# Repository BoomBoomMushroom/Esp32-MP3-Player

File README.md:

# ESP32 MP3 Player
An MP3 Player powered by an ESP32, with both bluetooth and a speaker output

I made this project because I want to move away from Spotify and own the songs I play. I have bought a dozen or two songs from bandcamp and that will be whats played on this!

Video of it working (Nothing here yet, still need funding)

Features:
- Seeed studio ESP32-S3 plus for the MCU and battery charging circuit
- A 2.8in ili9341 tft color screen
- MAX17048G+T10 for battery level checking
- a rotary encoder for input, and a vol up and vol down button
- MAX98357A + 8ohm 3W speakers for use w/o bluetooth headphones/speakers
- Any single cell LiPo works, im probably going to use a 2000mAh or 3000mAh battery

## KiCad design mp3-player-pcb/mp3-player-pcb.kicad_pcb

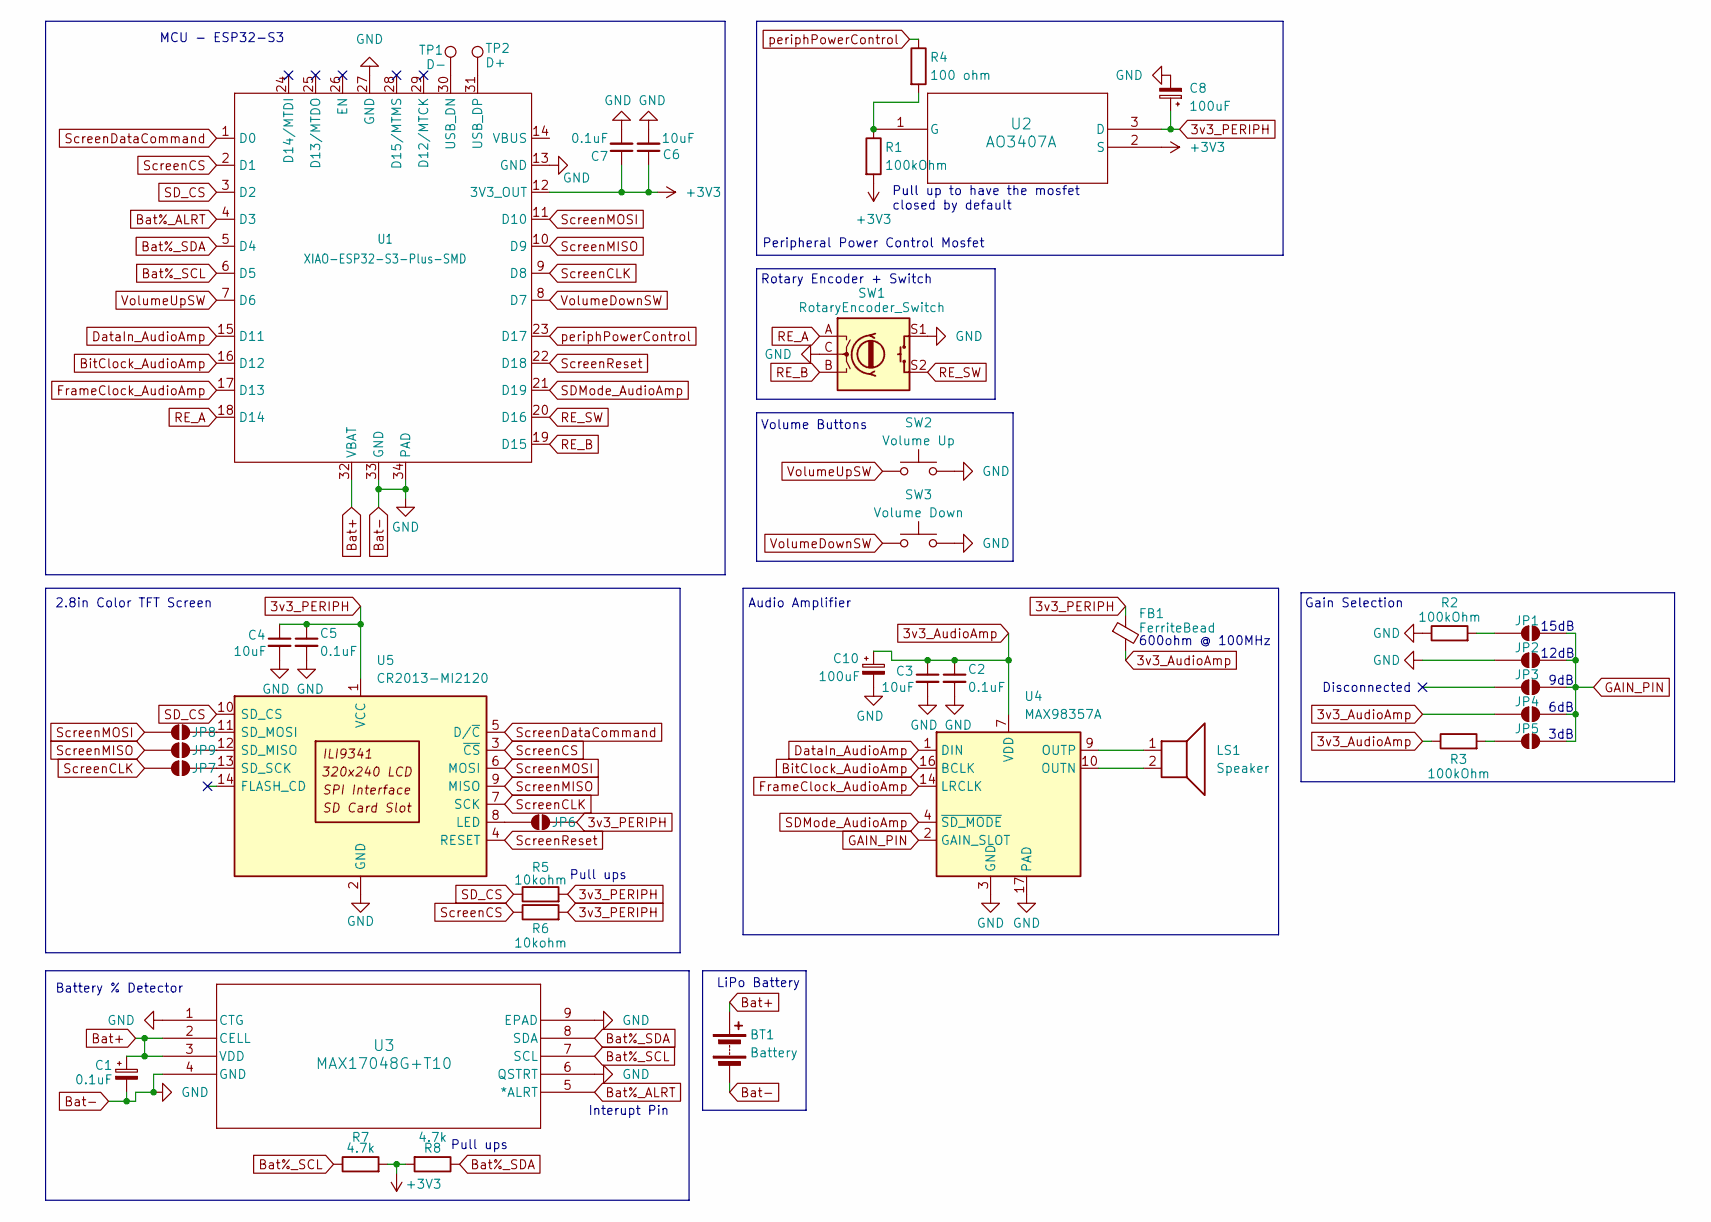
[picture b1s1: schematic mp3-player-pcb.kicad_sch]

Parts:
BT1: Battery; JST_EH_B2B-EH-A_1x02_P2.50mm_Vertical
C1: 0.1uF; CP_Radial_D4.0mm_P2.00mm
C2, C5, C7: 0.1uF; C_0603_1608Metric_Pad1.08x0.95mm_HandSolder
C3, C4, C6: 10uF; C_0603_1608Metric_Pad1.08x0.95mm_HandSolder
C8, C10: 100uF; CP_Radial_D4.0mm_P2.00mm
FB1: FerriteBead; C_0805_2012Metric_Pad1.18x1.45mm_HandSolder
JP1, JP2, JP3, JP4, JP5, JP6, JP7, JP8, JP9: SolderJumper_2_Open; SolderJumper-2_P1.3mm_Open_Pad1.0x1.5mm
LS1: Speaker; PinHeader_1x02_P2.54mm_Vertical
R1, R2, R3: 100kOhm; R_Axial_DIN0204_L3.6mm_D1.6mm_P5.08mm_Horizontal
R4: 100 ohm; R_Axial_DIN0204_L3.6mm_D1.6mm_P5.08mm_Horizontal
R5, R6: 10kohm; R_Axial_DIN0204_L3.6mm_D1.6mm_P5.08mm_Horizontal
R7, R8: 4.7k; R_Axial_DIN0204_L3.6mm_D1.6mm_P5.08mm_Horizontal
SW1: RotaryEncoder_Switch; RotaryEncoder_Bourns_Vertical_PEC12R-3x17F-Sxxxx
SW2: Volume Up; SW_Tactile_SPST_Angled_PTS645Vx58-2LFS
SW3: Volume Down; SW_Tactile_SPST_Angled_PTS645Vx58-2LFS
TP1: D-; TestPoint_Pad_D1.5mm
TP2: D+; TestPoint_Pad_D1.5mm
U1: XIAO-ESP32-S3-Plus-SMD
U2: AO3407A; SOT-23-3L_AOS
U3: MAX17048G+T10; 21-0168E_T822-3_MXM
U4: MAX98357A; TQFN-16-1EP_3x3mm_P0.5mm_EP1.23x1.23mm
U5: CR2013-MI2120

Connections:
3v3_AudioAmp: C2.1, C3.1, C10.1, FB1.2, JP4.1 (A), R3.1, U4.7 (VDD), U4.8 (VDD)
3v3_PERIPH: C4.1, C5.1, C8.1, FB1.1, JP6.2 (B), R5.2, R6.2, U2.3 (D), U5.1 (VCC)
+3V3: C6.1, C7.1, R1.2, R7.2, R8.2, U1.12 (3V3_OUT), U2.2 (S)
Bat%_ALRT: U1.4 (D3), U3.5 (*ALRT)
Bat%_SCL: R7.1, U1.6 (D5), U3.7 (SCL)
Bat%_SDA: R8.1, U1.5 (D4), U3.8 (SDA)
Bat+: BT1.1 (+), C1.1, U1.32 (VBAT), U3.2 (CELL), U3.3 (VDD)
Bat-: BT1.2 (-), C1.2, C2.2, C3.2, C4.2, C5.2, C6.2, C7.2, C8.2, C10.2, JP2.1 (A), R2.1, SW1.C, SW1.S1, SW2.2, SW3.2, U1.13 (GND), U1.27 (GND), U1.33 (GND), U1.34 (PAD), U3.1 (CTG), U3.4 (GND), U3.6 (QSTRT), U3.9 (EPAD), U4.3 (GND), U4.11 (GND), U4.15 (GND), U4.17 (PAD), U5.2 (GND)
BitClock_AudioAmp: U1.16 (D12), U4.16 (BCLK)
DataIn_AudioAmp: U1.15 (D11), U4.1 (DIN)
FrameClock_AudioAmp: U1.17 (D13), U4.14 (LRCLK)
GAIN_PIN: JP1.2 (B), JP2.2 (B), JP3.2 (B_2), JP4.2 (B), JP5.2 (B), U4.2 (GAIN_SLOT)
unnamed: JP1.1 (A), R2.2
unnamed: JP5.1 (A), R3.2
unnamed: JP6.1 (A), U5.8 (LED)
unnamed: JP7.2 (B), U5.13 (SD_SCK)
unnamed: JP8.2 (B), U5.11 (SD_MOSI)
unnamed: JP9.2 (B), U5.12 (SD_MISO)
unnamed: TP1.1 (1_1), U1.30 (USB_DN)
unnamed: TP2.1 (1_1), U1.31 (USB_DP)
unnamed: R1.1, R4.2, U2.1 (G)
unnamed: LS1.2, U4.10 (OUTN)
unnamed: LS1.1, U4.9 (OUTP)
RE_A: SW1.A, U1.18 (D14)
RE_B: SW1.B, U1.19 (D15)
RE_SW: SW1.S2, U1.20 (D16)
SDMode_AudioAmp: U1.21 (D19), U4.4 (~SD_MODE)
SD_CS: R5.1, U1.3 (D2), U5.10 (SD_CS)
ScreenCLK: JP7.1 (A), U1.9 (D8), U5.7 (SCK)
ScreenCS: R6.1, U1.2 (D1), U5.3 (~CS)
ScreenDataCommand: U1.1 (D0), U5.5 (D/~C)
ScreenMISO: JP9.1 (A), U1.10 (D9), U5.9 (MISO)
ScreenMOSI: JP8.1 (A), U1.11 (D10), U5.6 (MOSI)
ScreenReset: U1.22 (D18), U5.4 (RESET)
VolumeDownSW: SW3.1, U1.8 (D7)
VolumeUpSW: SW2.1, U1.7 (D6)
periphPowerControl: R4.1, U1.23 (D17)

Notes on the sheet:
Pull up to have the mosfet closed by default
600ohm @ 100MHz
2.8in Color TFT Screen
Volume Buttons
Rotary Encoder + Switch
6dB
Battery % Detector
Audio Amplifier
9dB
12dB
MCU - ESP32-S3
3dB
Gain Selection
Disconnected
Interupt Pin
Pull ups
LiPo Battery
15dB
Peripheral Power Control Mosfet

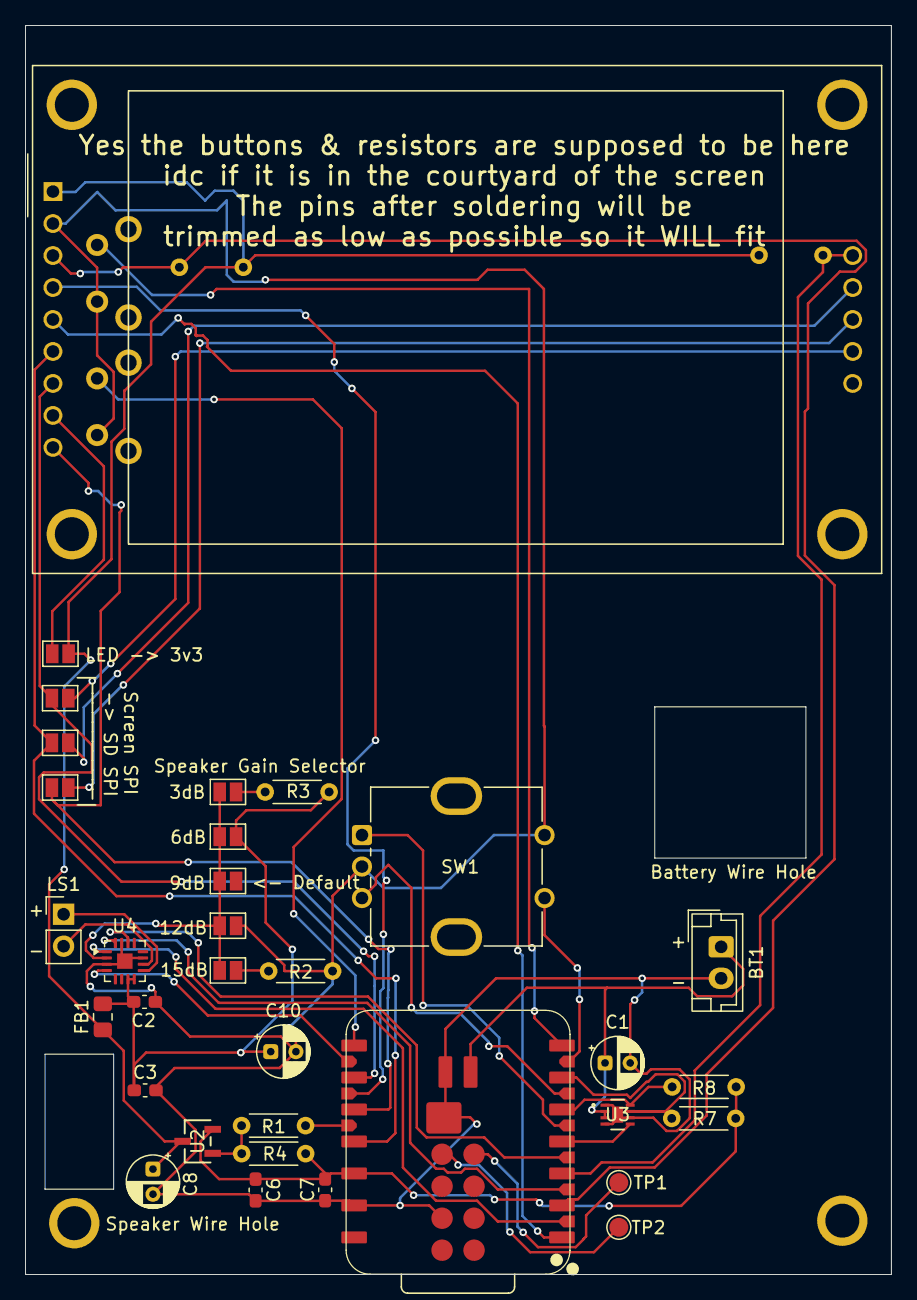
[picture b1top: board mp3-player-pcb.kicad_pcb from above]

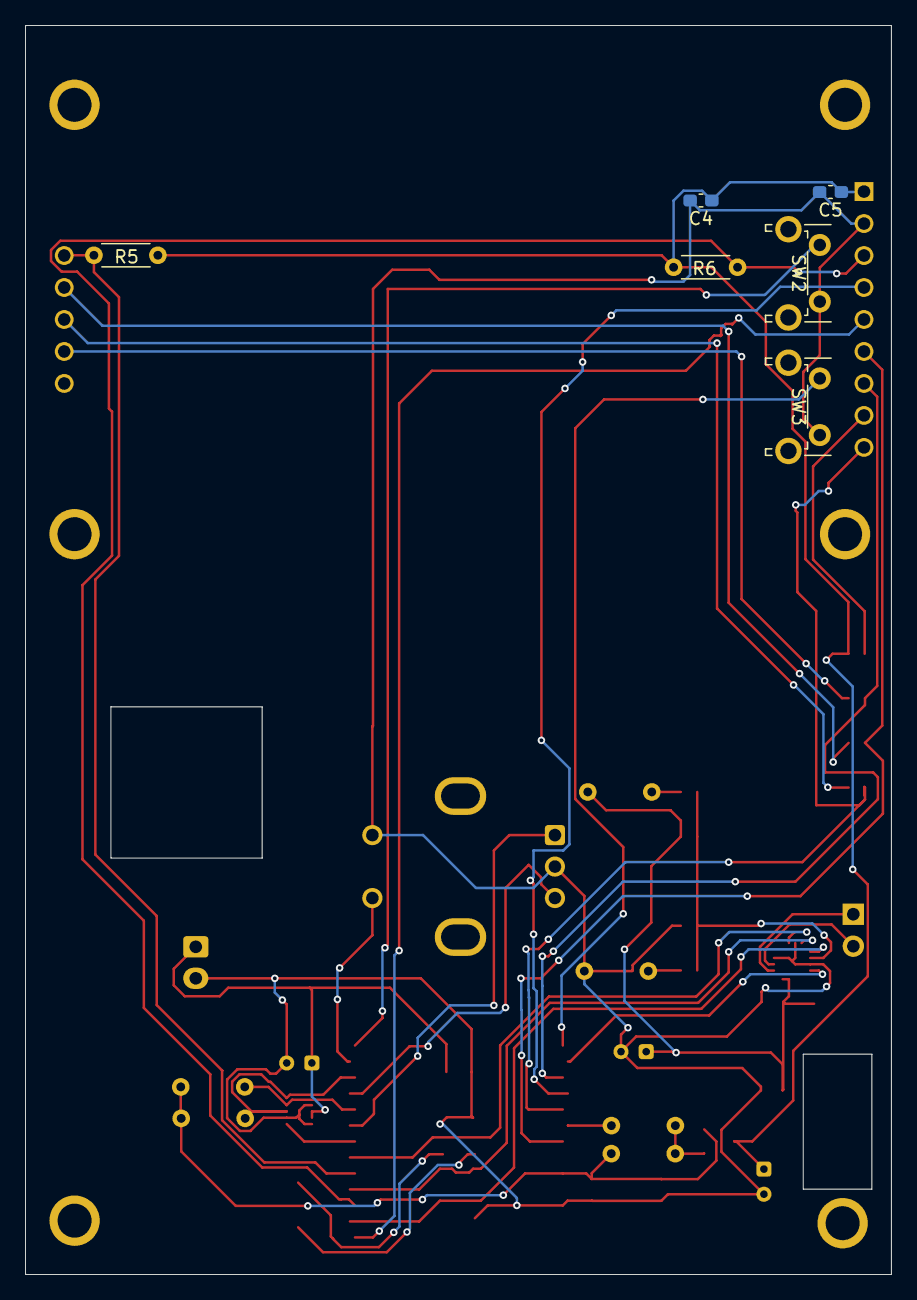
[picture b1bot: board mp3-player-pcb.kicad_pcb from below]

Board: 2 copper layers, 68.8 x 99.2 mm, 39 parts (6 on the bottom side), 37 nets.

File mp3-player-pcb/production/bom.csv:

Designator,Footprint,Quantity,Value,LCSC Part #
"_2, ",,2,,
BT1,JST_EH_B2B-EH-A_1x02_P2.50mm_Vertical,1,Battery,
C1,CP_Radial_D4.0mm_P2.00mm,1,0.1uF,
"C10, C8",CP_Radial_D4.0mm_P2.00mm,2,100uF,
"C2, C5, C7",0603,3,0.1uF,
"C3, C4, C6",0603,3,10uF,
FB1,0805,1,FerriteBead,
LS1,PinHeader_1x02_P2.54mm_Vertical,1,Speaker,
"R1, R2, R3",R_Axial_DIN0204_L3.6mm_D1.6mm_P5.08mm_Horizontal,3,100kOhm,
R4,R_Axial_DIN0204_L3.6mm_D1.6mm_P5.08mm_Horizontal,1,100 ohm,
"R5, R6",R_Axial_DIN0204_L3.6mm_D1.6mm_P5.08mm_Horizontal,2,10kohm,
"R7, R8",R_Axial_DIN0204_L3.6mm_D1.6mm_P5.08mm_Horizontal,2,4.7k,
SW1,RotaryEncoder_Bourns_Vertical_PEC12R-3x17F-Sxxxx,1,RotaryEncoder_Switch,
SW2,SW_Tactile_SPST_Angled_PTS645Vx58-2LFS,1,Volume Up,
SW3,SW_Tactile_SPST_Angled_PTS645Vx58-2LFS,1,Volume Down,
TP1,TestPoint_Pad_D1.5mm,1,D-,
TP2,TestPoint_Pad_D1.5mm,1,D+,
U1,XIAO-ESP32-S3-Plus-SMD,1,XIAO-ESP32-S3-Plus-SMD,
U2,SOT-23-3L_AOS,1,AO3407A,
U3,21-0168E_T822-3_MXM,1,MAX17048G+T10,
U4,TQFN-16-1EP_3x3mm_P0.5mm_EP1.23x1.23mm,1,MAX98357A,
U5,CR2013-MI2120,1,CR2013-MI2120,

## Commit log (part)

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2026-06-22 feat: schematic done and pcb layout finished, now have to route traces
2026-06-22 feat: finished routing the pcb
2026-06-27 feat: made case cad
2026-06-28 bom and other parts added
